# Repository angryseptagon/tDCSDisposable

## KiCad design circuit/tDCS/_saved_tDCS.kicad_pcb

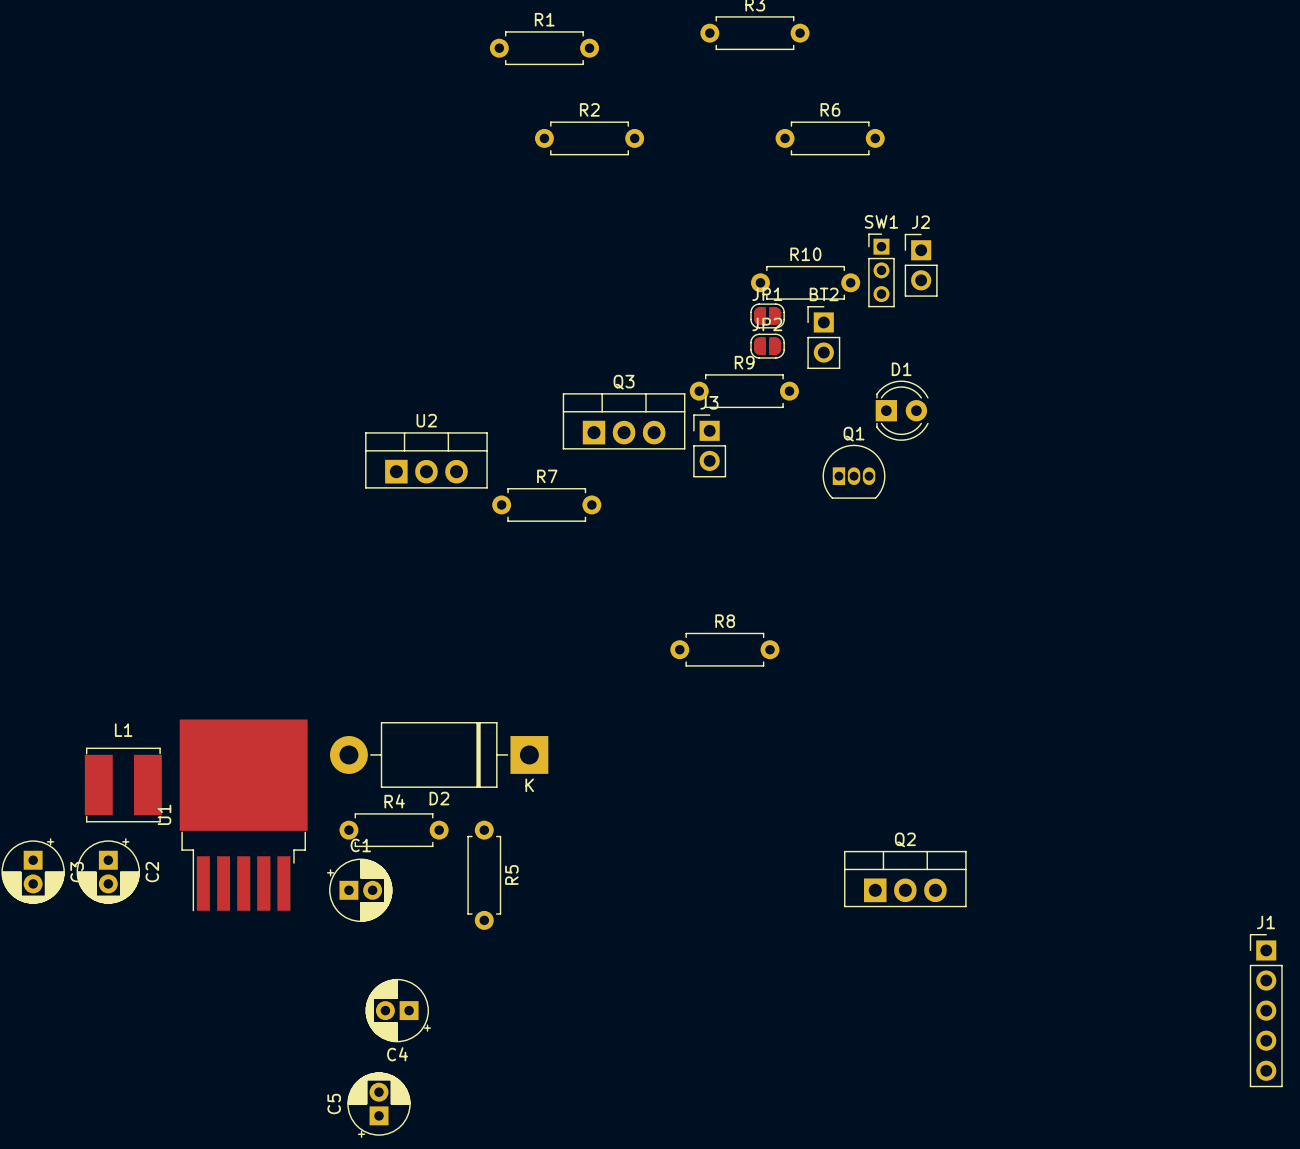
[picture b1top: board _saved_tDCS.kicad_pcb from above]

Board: 2 copper layers, 30 parts (0 on the bottom side), 18 nets, no tracks yet.

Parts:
BT2: Battery_Cell; PinHeader_1x02_P2.54mm_Vertical
C1: 10uf; CP_Radial_D5.0mm_P2.00mm
C2, C4: 220uF; CP_Radial_D5.0mm_P2.00mm
C3: 47uF; CP_Radial_D5.0mm_P2.00mm
C5: 100uF; CP_Radial_D5.0mm_P2.00mm
D1: DIODE; LED_D4.0mm
D2: 1N5821; D_DO-201AD_P15.24mm_Horizontal
J1: Conn_01x05_Male; PinHeader_1x05_P2.54mm_Vertical
J2, J3: Conn_01x02_Male; PinHeader_1x02_P2.54mm_Vertical
JP1, JP2: SolderJumper_2_Open; SolderJumper-2_P1.3mm_Open_RoundedPad1.0x1.5mm
L1: 33uh; L_Bourns_SRN6045TA
Q1: 2N3904; TO-92_Inline
Q2, Q3: IRL2203; TO-220-3_Vertical
R1, R9: 20k; R_Axial_DIN0207_L6.3mm_D2.5mm_P7.62mm_Horizontal
R2: 1.351 kOhm; R_Axial_DIN0207_L6.3mm_D2.5mm_P7.62mm_Horizontal
R3: 680; R_Axial_DIN0207_L6.3mm_D2.5mm_P7.62mm_Horizontal
R4: 31K; R_Axial_DIN0207_L6.3mm_D2.5mm_P7.62mm_Horizontal
R5: 1K; R_Axial_DIN0207_L6.3mm_D2.5mm_P7.62mm_Horizontal
R6: 10k; R_Axial_DIN0207_L6.3mm_D2.5mm_P7.62mm_Horizontal
R7: 1 Ohm; R_Axial_DIN0207_L6.3mm_D2.5mm_P7.62mm_Horizontal
R8, R10: 10 kOhm; R_Axial_DIN0207_L6.3mm_D2.5mm_P7.62mm_Horizontal
SW1: SW_SPDT; PinHeader_1x03_P2.00mm_Vertical
U1: XL6009; TO-263-5_TabPin3
U2: L7805; TO-220-3_Vertical

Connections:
+5V: J1.2, U2.3
+9V: BT2.1, JP1.1, U1.2, U2.1
unnamed: C1.1, D2.1, JP2.1, R4.1
unnamed: C1.2, R4.2, R5.1, U1.5
unnamed: C2.1, C3.1, L1.1, SW1.3, U1.4
unnamed: C5.1, Q2.1, R6.1, R10.1
unnamed: D1.1, Q1.2, Q2.2, R1.1
unnamed: D2.2, L1.2, U1.3
unnamed: J1.1, Q3.3, R7.1
unnamed: J1.4, Q3.1, R8.1
unnamed: J1.5, R6.2
unnamed: J3.1, Q1.3
unnamed: J3.2, R3.1, R9.2
unnamed: JP1.2, SW1.2
unnamed: Q1.1, R2.1
unnamed: Q3.2, R9.1
boostout+: C4.1, J2.2, JP2.2, R1.2, R3.2
boostout-: BT2.2, C2.2, C3.2, C4.2, C5.2, D1.2, J1.3, J2.1, Q2.3, R2.2, R5.2, R7.2, R8.2, R10.2, U1.1, U2.2

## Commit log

2021-02-18 initial upload
    disposable tDCS project
